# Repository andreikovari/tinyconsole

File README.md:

# tinyconsole
Attiny85 based gaming console

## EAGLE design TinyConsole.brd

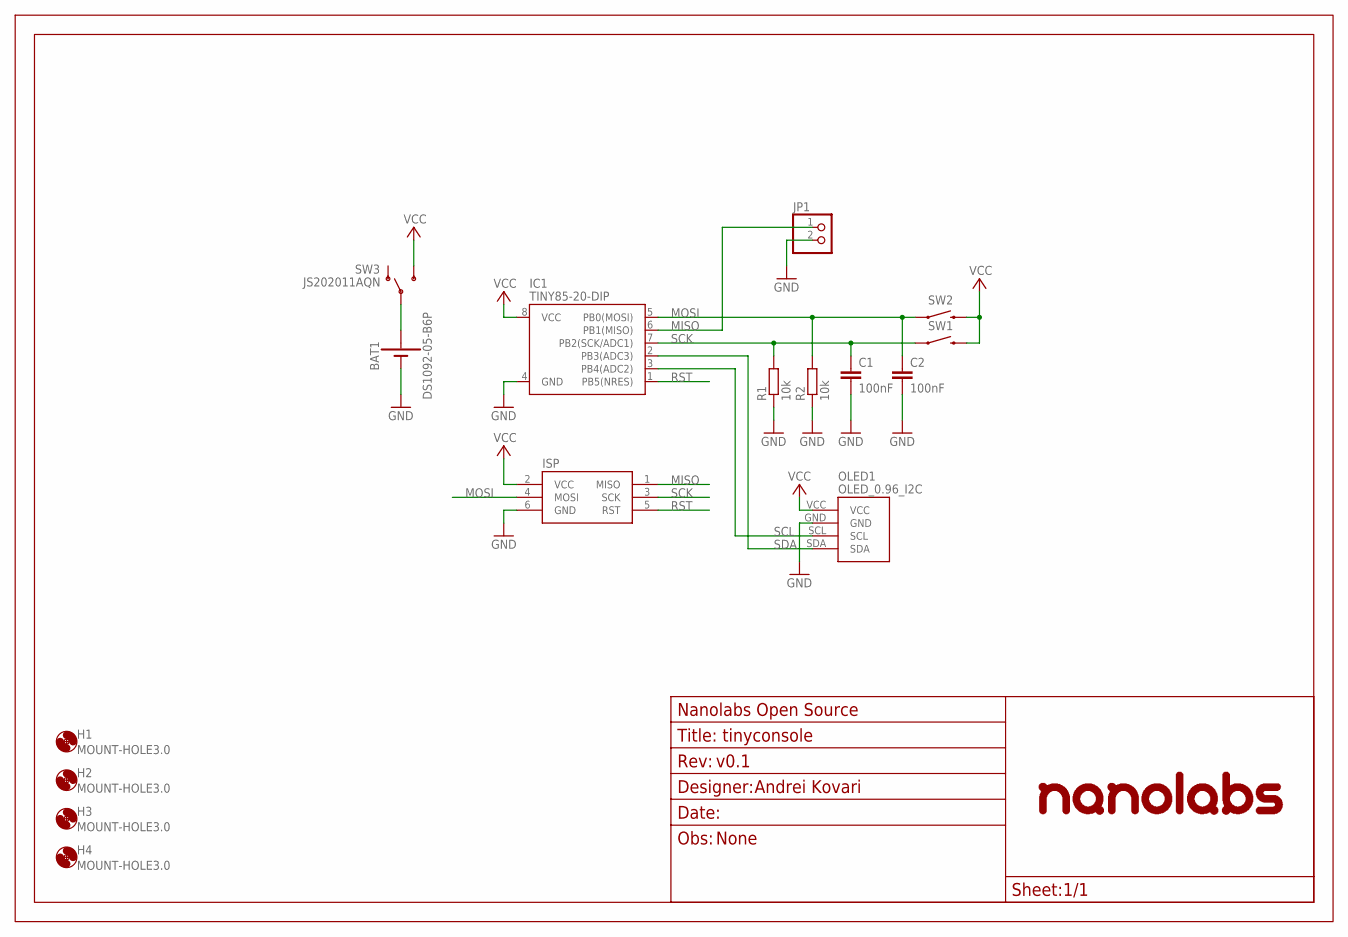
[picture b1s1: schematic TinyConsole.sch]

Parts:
BAT1: DS1092-05-B6P
C1, C2: 100nF; C050-025X075
FRAME1: Nanolabs Open Source; DOCU
H1, H2, H3, H4: MOUNT-HOLE3.0; 3,0
IC1: TINY85-20-DIP; DIP08
ISP: AVRISP-6; AVRISP
JP1: PINHD-1X2; 1X02
OLED1: OLED_0.96_I2C
R1, R2: 10k; 0207/7
SW1, SW2: SWITCH-MOMENTARY-212MM; TACTILE-PTH-12MM
SW3: JS202011AQN

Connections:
GND: BAT1.-, C1.2, C2.2, IC1.4 (GND), ISP.6 (GND), JP1.2, OLED1.GND, R1.1, R2.1
MISO: IC1.6 (PB1(MISO)), ISP.1 (MISO), JP1.1
MOSI: C2.1, IC1.5 (PB0(MOSI)), ISP.4 (MOSI), R2.2, SW2.1
unnamed: BAT1.+, SW3.2 (COM), SW3.5 (COM)
RST: IC1.1 (PB5(NRES)), ISP.5 (RST)
SCK: C1.1, IC1.7 (PB2(SCK/ADC1)), ISP.3 (SCK), R1.2, SW1.1
SCL: IC1.3 (PB4(ADC2)), OLED1.SCL
SDA: IC1.2 (PB3(ADC3)), OLED1.SDA
VCC: IC1.8 (VCC), ISP.2 (VCC), OLED1.VCC, SW1.3 (2), SW2.3 (2), SW3.3 (NO), SW3.6 (NO)

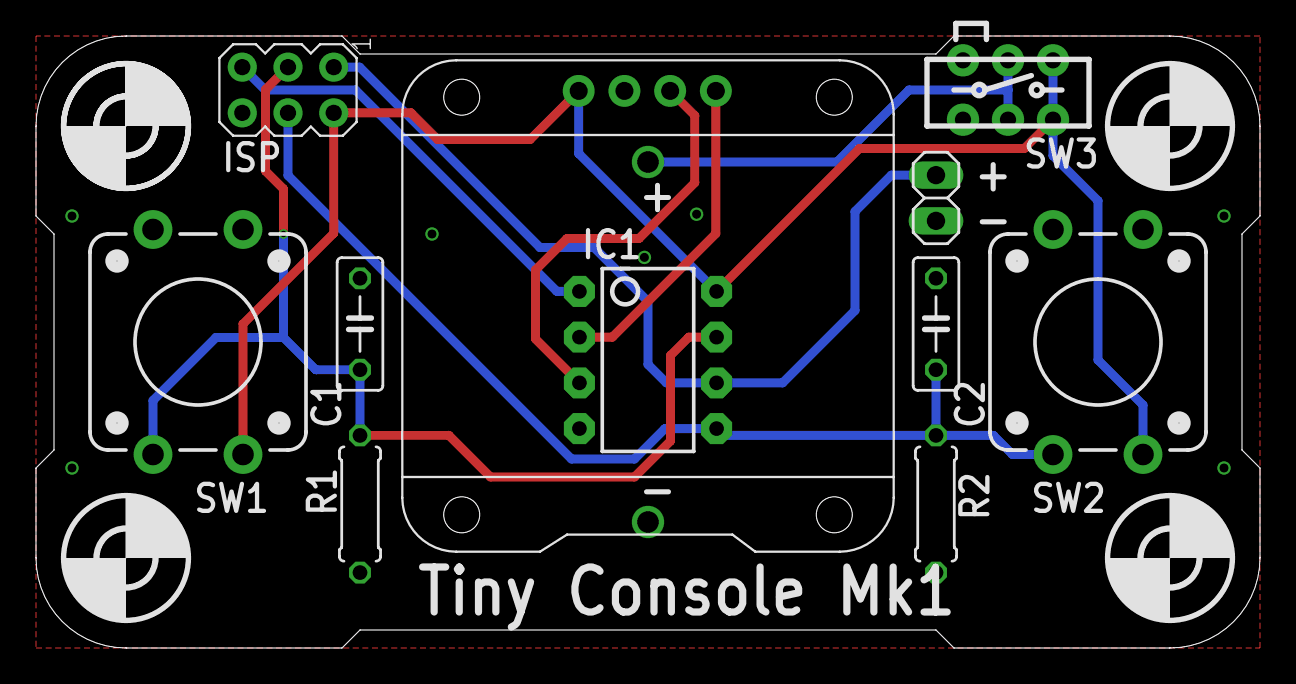
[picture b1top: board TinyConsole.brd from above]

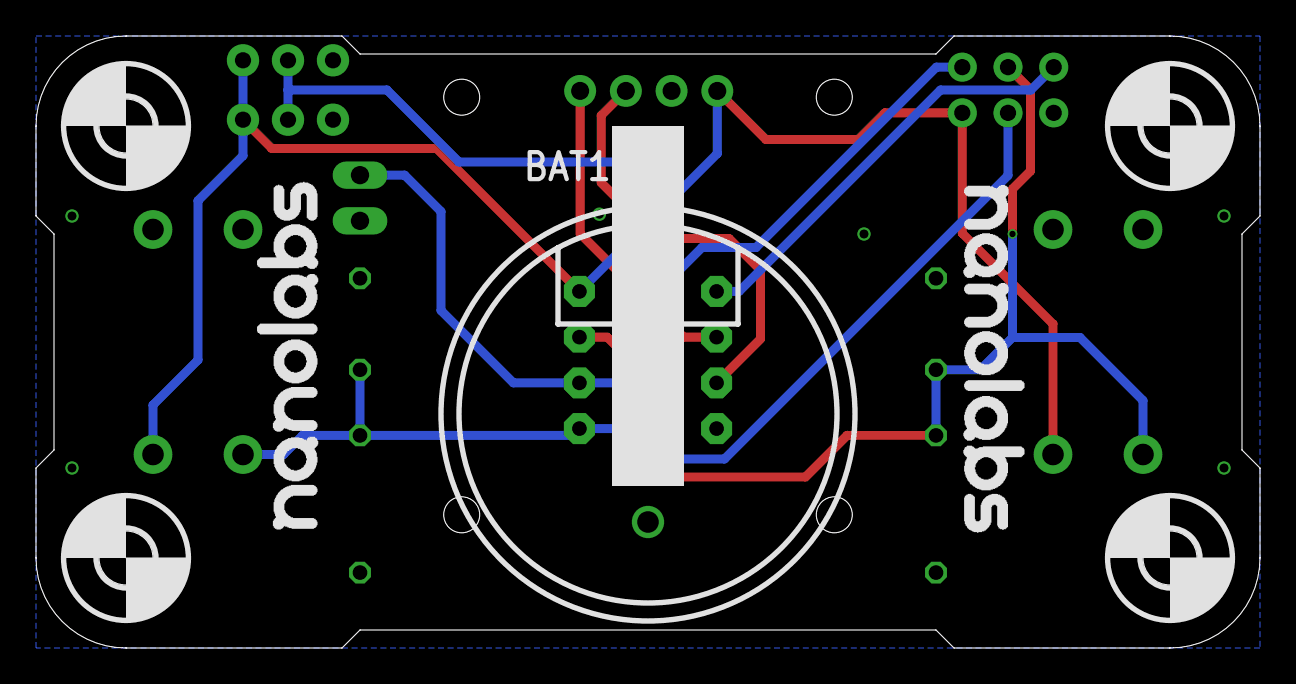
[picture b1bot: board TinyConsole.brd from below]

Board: 2 copper layers, 68.0 x 34.0 mm, 19 parts (3 on the bottom side), 9 nets.

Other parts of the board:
U$1, U$2: NANOLOGO1

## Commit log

2021-02-15 Create LICENSE

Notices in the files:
parts and their libraries:
SparkFun-Electromechanical: Licensing: Creative Commons ShareAlike 4.0 International - https://creativecommons.org/licenses/by-sa/4.0
